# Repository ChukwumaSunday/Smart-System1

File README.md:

Pro-Tracking 4G LTE Solution Board
Pro-Tracking Solution Board is an ecosystem friendly onboard tracking technology and multi-functional development board based on STM32 microcontroller, designed to meet the requirements of embedded systems, vehicles/general tracking, providing a comprehensive set of features and peripherals on a single chip. The system is optimized for low power consumption and real-time processing, making it suitable for a wide rand of application
Pro-Tracking 4G LTE offers wide range of capabilities and features, making it ideal for use in many different types of applications.  This system can be used in consumer products such as appliances remote controls, motor control systems, medical devices, gaming console, home automation systems and more.
A Pro-Tracking 4G LTE integrated two types of the 4G LTE CAT4 module SIM7600A-H or SIM7600E-H, SIM7600A-H/SIM7600E-H is a complete multi-band LTE-FDD/LTE-TDD/HSPA+/UMTS/EDGE/GPRS/GSM module solution in LCC type which supports LTE CAT4 up to 150Mbps for downlink and 50Mbps for uplink data transfer, much faster and popular than 2G/3G.
 
Board Interface 

Features
•	Supports dial-up, phone, SMS, TCP, UDP, DTMF, HTTP, FTP, and so on
•	Dual USB Type C port
•	Control Via AT Commands
•	Board USB supply voltage range: 4.8~5.5V, 5.0V Typical
•	Board Battery supply voltage range: 3.4~4.2V, 3.7V Typical
•	3GPP E-UTRA Release 11
•	Onboard charger, up to 1A charge current
•	Overcharge protection(OCP), 4.3V
•	Over-discharge protection(ODP), 2.5V
•	Power Manager, the board can be supplied by USB or battery.
•	IPEX Antenna, GSM/UMTS/LTE main antenna. UMTS/LTE auxiliary antenna. GNSS antenna
•	SMS support
•	Audio support
•	On board controller: STM32F411CEU6
•	Support  STM32CUBE IDE 
•	Audio Codec: NAU8810
•	Level Shifter: TXS0108E
•	Windows and Raspberry Pi support
•	Qualcomm MDM9x07 Chipset
•	On  board Sensor : MPU-6050 (Accelerometer/Gyroscope)
•	On  board Sensor 256MB flash memory: W25Q32JVSSIQ
Current Stage
The PCB development stage is almost done
Challenges
•	Time
•	Sourcing of component
•	Getting quality component elements
Requirements
Finance to fund the project

Usage
Warning: Do not operate when in power on (don’t plug or unplug the Antenna, SIM Cards, SD Card, in case of short-circuiting that may burn the IC down.)
Hardware connection
1. Plug the SIM card into the board.
2. Plug the GPS antenna into the interface.
3. Plug two 4G-GSM antennas into the main antenna interface and auxiliary one.
4. Plug the headphone with the microphone.
5. Plug the SD card into the SD card slot for SIM7600.
When powering the board and the SIM7600 module working, the onboard STA LED (blue) will turn on.
Possible projects with Pro-tracking Solution Board
1.	GPS Tracker - SMS & Battery Monitor 
2.	Send Location & Make Call using SOS Button _ IOT Projects _ GPS Projects
3.	Embedded Systems applications
4.	IoT applications
5.	This system can be used in consumer products such as 
•	Appliances remote controls
•	Vehicles/Location Tracking
•	Motor control systems
•	Medical devices
•	Gaming console
•	Home automation systems and more.

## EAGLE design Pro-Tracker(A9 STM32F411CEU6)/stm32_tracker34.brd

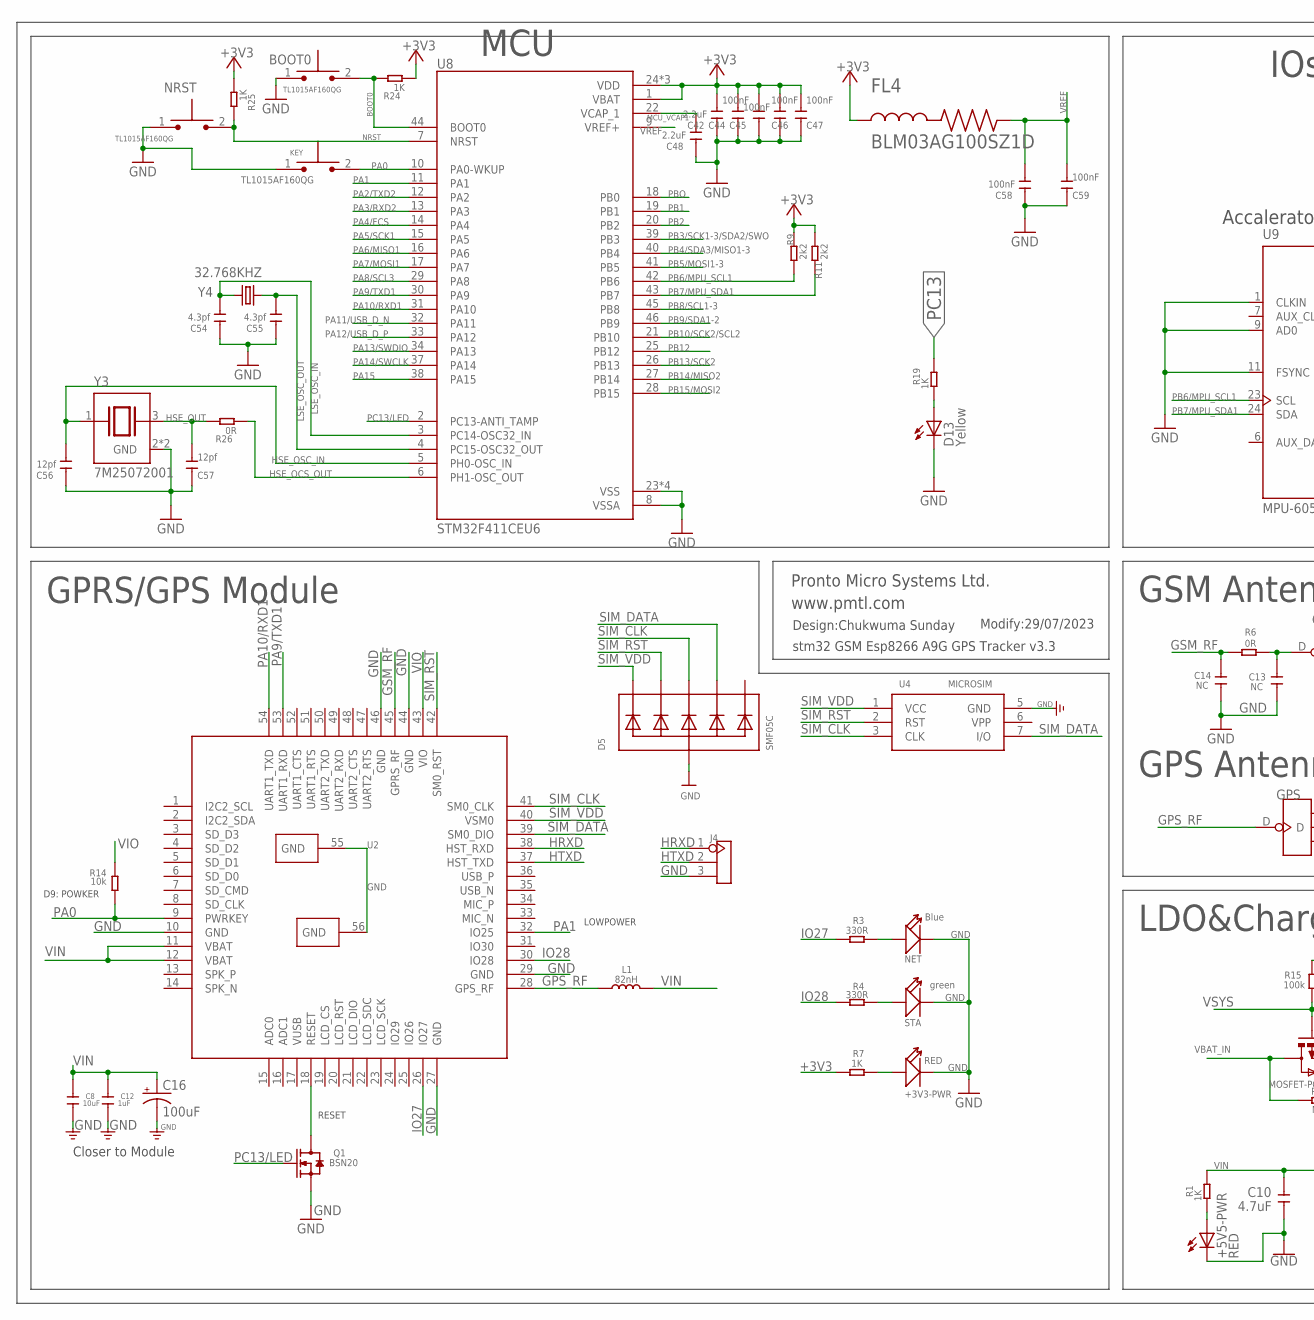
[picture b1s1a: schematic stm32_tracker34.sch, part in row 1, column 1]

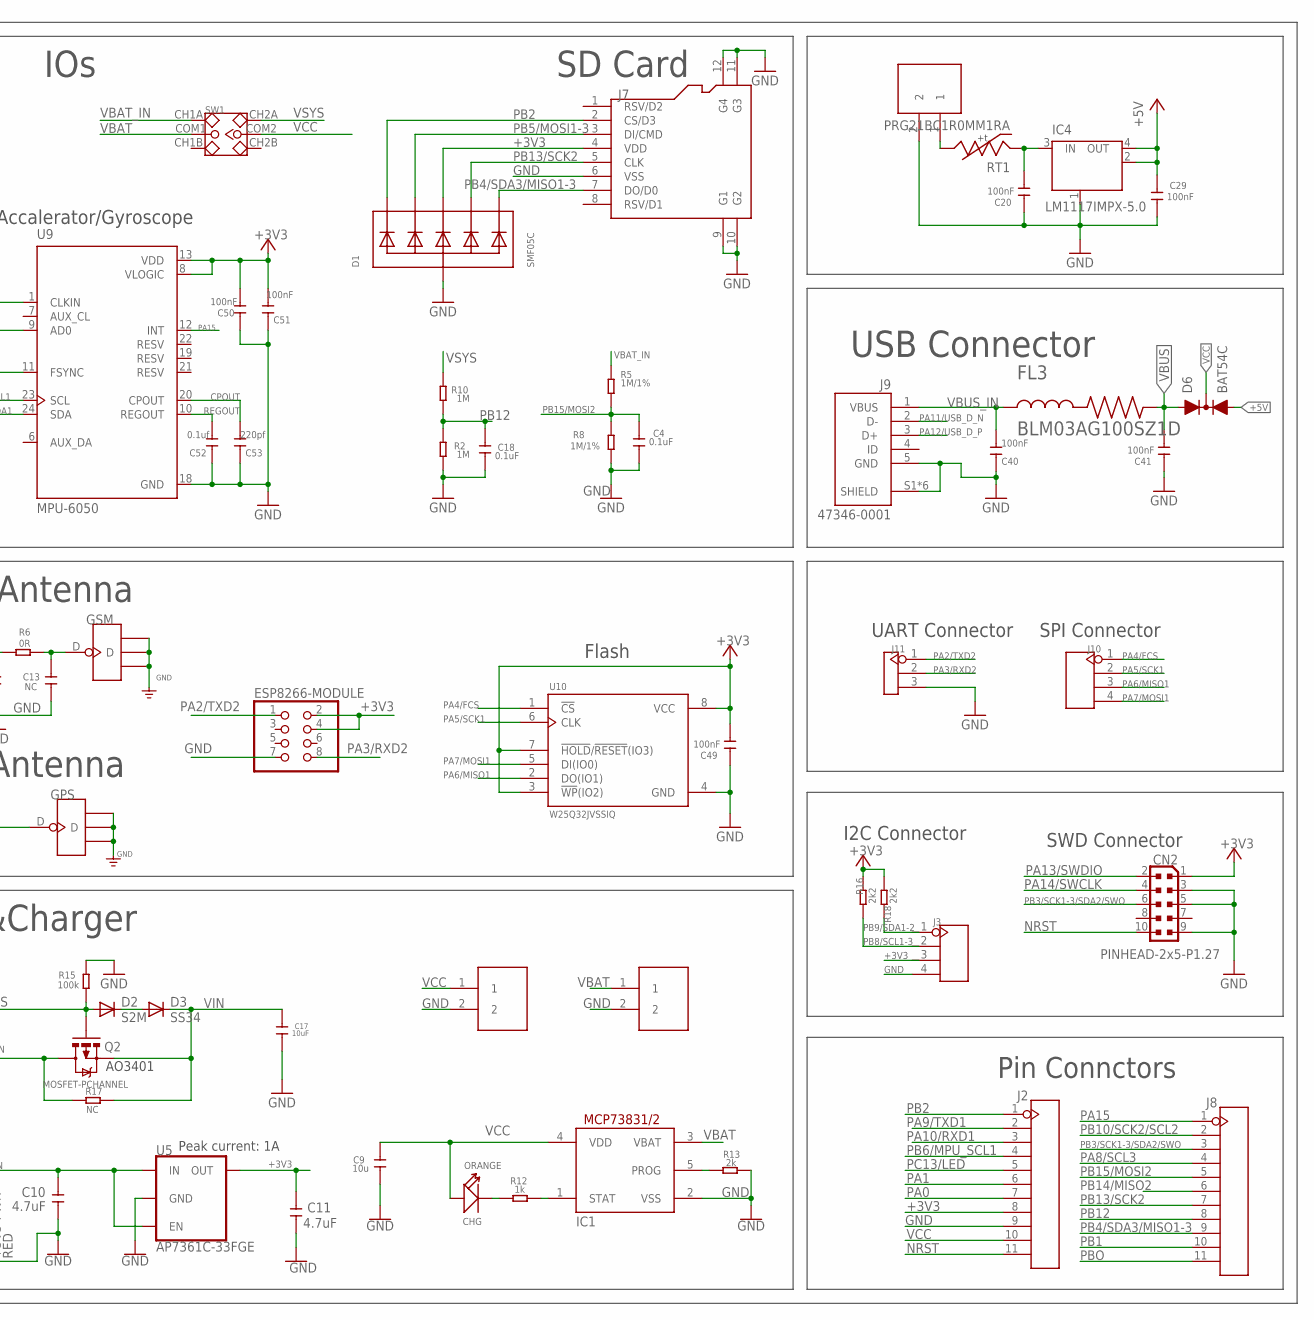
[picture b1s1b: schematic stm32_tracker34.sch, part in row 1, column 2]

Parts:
+3V3-PWR: RED; LED-0603
+5V5-PWR: RED; OPTO_CHIPLED_0805
BOOT0: TL1015AF160QG; SW_TL1015AF160QG
C4, C18: 0.1uF; C0603
C8, C17: 10uF; C0603
C9: 10u; C0603
C10, C11: 4.7uF; C0603
C12: 1uF; C0603
C13, C14: NC; C0402
C16: 100uF; EIA3528
C20, C29, C40, C41, C44, C45, C46, C47, C49, C50, C51, C58, C59: 100nF; C0603
C42, C48: 2.2uF; C0603
C52: 0.1uf; C0603
C53: 220pf; C0603
C54, C55: 4.3pf; C0603
C56, C57: 12pf; C0603
CHG: ORANGE; D0603
CN2: PINHEAD-2x5-P1.27; PINHEAD_2X05_127
D1, D5: SMF05C; SOT363
D2: S2M; DO-214AC
D3: SS34; DO-214AC
D6: BAT54C; SOT23-R
D13: Yellow; OPTO_CHIPLED_0805
ESP8266-MODULE: PINHD-2X4; 2X04
FL3, FL4: BLM03AG100SZ1D; BEADC0603X33N
GPS: ANTENNA-U-FL; 4P-U-FL
GSM: ANTENNA-U-FL; 4P-U-FL
IC1: MCP73831/OT; SOT23-5L
IC4: LM1117IMPX-5.0; INTEGRATEDCIRCUITS_LINEAR_SOT223
J1, J5, J6: PH2.0-2P-90-DIP
J2, J8: HEADER-11P-2.54; 11P-2.54
J3, J10: HEADER-4P-60/35MILROUND; 4P-65/35ROUND
J4, J11: HEADER-3P-2.54; 3P-2.54
J7: HOLDER-MICROSD-8P; 8P-SMD
J9: 47346-0001; MOLEX_47346-0001
KEY: TL1015AF160QG; SW_TL1015AF160QG
L1: 82nH; L0603
NET: Blue; LED-0603
NRST: TL1015AF160QG; SW_TL1015AF160QG
Q1: BSN20; SOT23@1
Q2: MOSFET-PCHANNEL; SOT23-3
R1, R7, R19, R24, R25: 1K; R0603
R2, R10: 1M; R0603
R3, R4: 330R; R0603
R5, R8: 1M/1%; R0603
R6, R26: 0R; R0603
R9, R11, R16, R18: 2k2; R0603
R12: 1k; R0603
R13: 2k; R0603
R14: 10k; R0603
R15: 100k; R0603
R17: NC; R0603
RT1: PRG21BC1R0MM1RA; THRMC2012X110N
STA: green; LED-0603
SW1: SWITCH-2CH-6P; 6P-2CH-2.54-7.6X3.0
U2: A9G
U4: MICROSIM
U5: AP7361C-33FGE; 8-UDFN
U8: STM32F411CEU6; QFN50P700X700X60-49N
U9: MPU-6050; QFN50P400X400X95-24N
U10: W25Q32JVSSIQ; SOIC127P790X216-8N
Y3: 7M25072001; XTAL_7M25072001
Y4: 32.768KHZ; XTAL160X100X50

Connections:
+3V3: C11.2, C42.2, C44.2, C45.2, C46.2, C47.2, C49.2, C50.2, C51.2, CN2.1, D1.4 (C3), ESP8266-MODULE.2, ESP8266-MODULE.4, FL4.1, J2.8, J3.3, J7.4 (VDD), R7.1, R9.1, R11.1, R16.1, R18.1, R24.1, R25.1, U5.1 (OUT), U8.1 (VBAT), U8.24 (VDD), U8.36 (VDD), U8.48 (VDD), U9.8 (VLOGIC), U9.13 (VDD), U10.3 (!WP!(IO2)), U10.7 (!HOLD!/!RESET!(IO3)), U10.8 (VCC)
+5V: C29.1, D6.2 (A2), IC4.2 (OUT), IC4.4 (OUT)
A9_RESET: Q1.3 (D), U2.18 (RESET)
BOOT0: BOOT0.2, R24.2, U8.44 (BOOT0)
CPOUT: C53.2, U9.20 (CPOUT)
GND: +3V3-PWR.-, +5V5-PWR.C, BOOT0.1, C4.2, C8.1, C9.1, C10.1, C11.1, C12.1, C13.1, C14.1, C16.C (-), C17.1, C18.2, C20.1, C29.2, C40.1, C41.1, C42.1, C44.1, C45.1, C46.1, C47.1, C48.1, C49.1, C50.1, C51.1, C52.1, C53.1, C54.1, C55.1, C56.1, C57.1, C58.1, C59.1, CN2.3, CN2.5, CN2.9, D1.2 (A), D5.2 (A), D13.C, ESP8266-MODULE.7, GPS.GND1, GPS.GND2, GPS.GND3, GSM.GND1, GSM.GND2, GSM.GND3, IC1.2 (VSS), IC4.1 (GND/ADJ), J1.2, J2.9, J3.4, J4.3, J5.2, J6.2, J7.6 (VSS), J7.9 (G1), J7.10 (G2), J7.11 (G3), J7.12 (G4), J9.5 (GND), J9.S1 (SHIELD), J9.S2 (SHIELD), J9.S3 (SHIELD), J9.S4 (SHIELD), J9.S5 (SHIELD), J9.S6 (SHIELD), J11.3, KEY.1, NET.-, NRST.1, Q1.2 (S), R2.1, R8.1, R13.2, R15.2, STA.-, U2.10 (GND), U2.27 (GND), U2.29 (GND), U2.44 (GND), U2.46 (GND), U2.55 (GND), U2.56 (GND), U4.5 (GND), U5.4 (GND), U5.EP (GND), U8.8 (VSSA), U8.23 (VSS), U8.35 (VSS), U8.47 (VSS), U8.49 (VSS), U9.1 (CLKIN), U9.9 (AD0), U9.11 (FSYNC), U9.18 (GND), U10.4 (GND), Y3.2 (GND), Y3.4 (GND)
GPS_RF: GPS.D, L1.1, U2.28 (GPS_RF)
GSM_RF: C14.2, R6.1, U2.45 (GPRS_RF)
HRXD: J4.1, U2.38 (HST_RXD)
HSE_OCS_OUT: R26.1, U8.6 (PH1-OSC_OUT)
HSE_OSC_IN: C56.2, U8.5 (PH0-OSC_IN), Y3.1
HSE_OUT: C57.2, R26.2, Y3.3 (2)
HTXD: J4.2, U2.37 (HST_TXD)
IO27: R3.1, U2.26 (IO27)
IO28: R4.1, U2.30 (IO28)
LSE_OSC_IN: C54.2, U8.3 (PC14-OSC32_IN), Y4.2
LSE_OSC_OUT: C55.2, U8.4 (PC15-OSC32_OUT), Y4.1
MCU_VCAP1: C48.2, U8.22 (VCAP_1)
unnamed: R4.2, STA.+
unnamed: D2.C, D3.A
unnamed: +3V3-PWR.+, R7.2
unnamed: J5.1, RT1.2
unnamed: +5V5-PWR.A, R1.1
unnamed: C20.2, IC4.3 (IN), RT1.1
unnamed: NET.+, R3.2
unnamed: D13.A, R19.1
unnamed: CHG.-, R12.1
unnamed: IC1.1 (STAT), R12.2
unnamed: IC1.5 (PROG), R13.1
unnamed: C13.2, GSM.D, R6.2
NRST: CN2.10, J2.11, NRST.2, R25.2, U8.7 (NRST)
PA0: J2.7, KEY.2, R14.1, U2.9 (PWRKEY), U8.10 (PA0-WKUP)
PA1: J2.6, U2.32 (IO25), U8.11 (PA1)
PA2/TXD2: ESP8266-MODULE.1, J11.1, U8.12 (PA2)
PA3/RXD2: ESP8266-MODULE.8, J11.2, U8.13 (PA3)
PA4/FCS: J10.1, U8.14 (PA4), U10.1 (!CS)
PA5/SCK1: J10.2, U8.15 (PA5), U10.6 (CLK)
PA6/MISO1: J10.3, U8.16 (PA6), U10.2 (DO(IO1))
PA7/MOSI1: J10.4, U8.17 (PA7), U10.5 (DI(IO0))
PA8/SCL3: J8.4, U8.29 (PA8)
PA9/TXD1: J2.2, U2.53 (UART1_RXD), U8.30 (PA9)
PA10/RXD1: J2.3, U2.54 (UART1_TXD), U8.31 (PA10)
PA11/USB_D_N: J9.2 (D-), U8.32 (PA11)
PA12/USB_D_P: J9.3 (D+), U8.33 (PA12)
PA13/SWDIO: CN2.2, U8.34 (PA13)
PA14/SWCLK: CN2.4, U8.37 (PA14)
PA15: J8.1, U8.38 (PA15), U9.12 (INT)
PB1: J8.10, U8.19 (PB1)
PB2: D1.1 (C1), J2.1, J7.2 (CS/D3), U8.20 (PB2)
PB3/SCK1-3/SDA2/SWO: CN2.6, J8.3, U8.39 (PB3)
PB4/SDA3/MISO1-3: D1.6 (C5), J7.7 (DO/D0), J8.9, U8.40 (PB4)
PB5/MOSI1-3: D1.3 (C2), J7.3 (DI/CMD), U8.41 (PB5)
PB6/MPU_SCL1: J2.4, R9.2, U8.42 (PB6), U9.23 (SCL)
PB7/MPU_SDA1: R11.2, U8.43 (PB7), U9.24 (SDA)
PB8/SCL1-3: J3.2, R16.2, U8.45 (PB8)
PB9/SDA1-2: J3.1, R18.2, U8.46 (PB9)
PB10/SCK2/SCL2: J8.2, U8.21 (PB10)
PB12: C18.1, J8.8, R2.2, R10.1, U8.25 (PB12)
PB13/SCK2: D1.5 (C4), J7.5 (CLK), J8.7, U8.26 (PB13)
PB14/MISO2: J8.6, U8.27 (PB14)
PB15/MOSI2: C4.1, J8.5, R5.1, R8.2, U8.28 (PB15)
PBO: J8.11, U8.18 (PB0)
PC13: R19.2
PC13/LED: J2.5, Q1.1 (G), U8.2 (PC13-ANTI_TAMP)
REGOUT: C52.2, U9.10 (REGOUT)
SIM_CLK: D5.4 (C3), U2.41 (SM0_CLK), U4.3 (CLK)
SIM_DATA: D5.5 (C4), U2.39 (SM0_DIO), U4.7 (I/O)
SIM_RST: D5.3 (C2), U2.42 (SM0_RST), U4.2 (RST)
SIM_VDD: D5.1 (C1), U2.40 (VSM0), U4.1 (VCC)
VBAT: IC1.3 (VBAT), J6.1, SW1.COM1
VBAT_IN: Q2.3 (D), R5.2, R17.1, SW1.CH1A
VBUS: C41.2, D6.1 (A1), FL3.2
VBUS_IN: C40.2, FL3.1, J9.1 (VBUS)
VCC: C9.2, CHG.+, D6.3 (C), IC1.4 (VDD), J1.1, J2.10, SW1.COM2
VIN: C8.2, C10.2, C12.2, C16.A (+), C17.2, D3.C, L1.2, Q2.2 (S), R1.2, R17.2, U2.11 (VBAT), U2.12 (VBAT), U5.5 (EN), U5.8 (IN)
VIO: R14.2, U2.43 (VIO)
VREF: C58.2, C59.2, FL4.2, U8.9 (VREF+)
VSYS: D2.A, Q2.1 (G), R10.2, R15.1, SW1.CH2A

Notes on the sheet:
GSM Antenna
GPRS/GPS Module
LOWPOWER
RESET
D9: POWKER
Peak current: 1A
www.pmtl.com
IOs
LDO&Charger
GPS Antenna
Design:Chukwuma Sunday
Modify:29/07/2023
Pronto Micro Systems Ltd.
Closer to Module
AO3401
stm32 GSM Esp8266 A9G GPS Tracker v3.3
MCU
USB Connector
Flash
SWD Connector
Accalerator/Gyroscope
Pin Connctors
SD Card
SPI Connector
UART Connector
I2C Connector

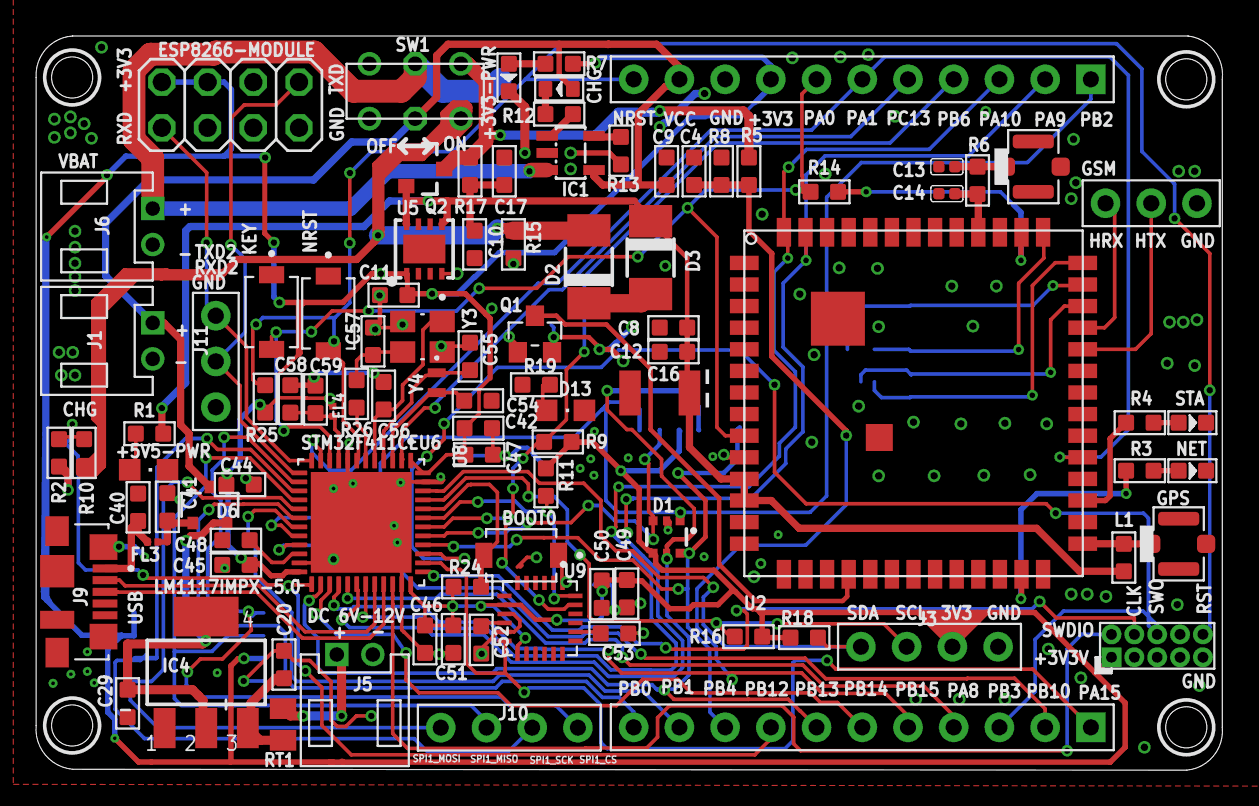
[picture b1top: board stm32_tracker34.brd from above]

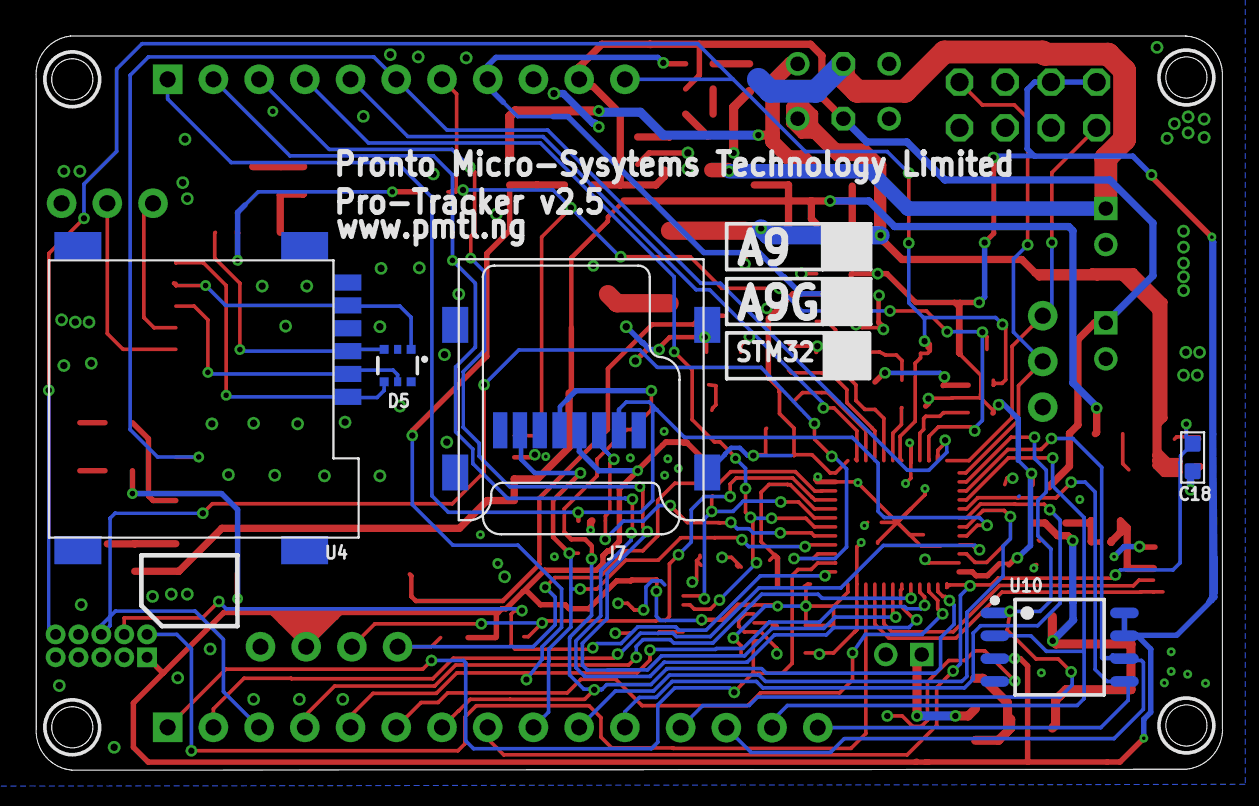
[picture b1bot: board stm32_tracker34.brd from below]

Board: 2 copper layers, 65.9 x 40.8 mm, 100 parts (5 on the bottom side), 77 nets.

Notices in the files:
parts and their libraries:
microbuilder: This work is placed in the public domain, and may be freely used for commercial and non-commercial work with the following conditions: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
SparkFun-Capacitors: Licensing: Creative Commons ShareAlike 4.0 International - https://creativecommons.org/licenses/by-sa/4.0
